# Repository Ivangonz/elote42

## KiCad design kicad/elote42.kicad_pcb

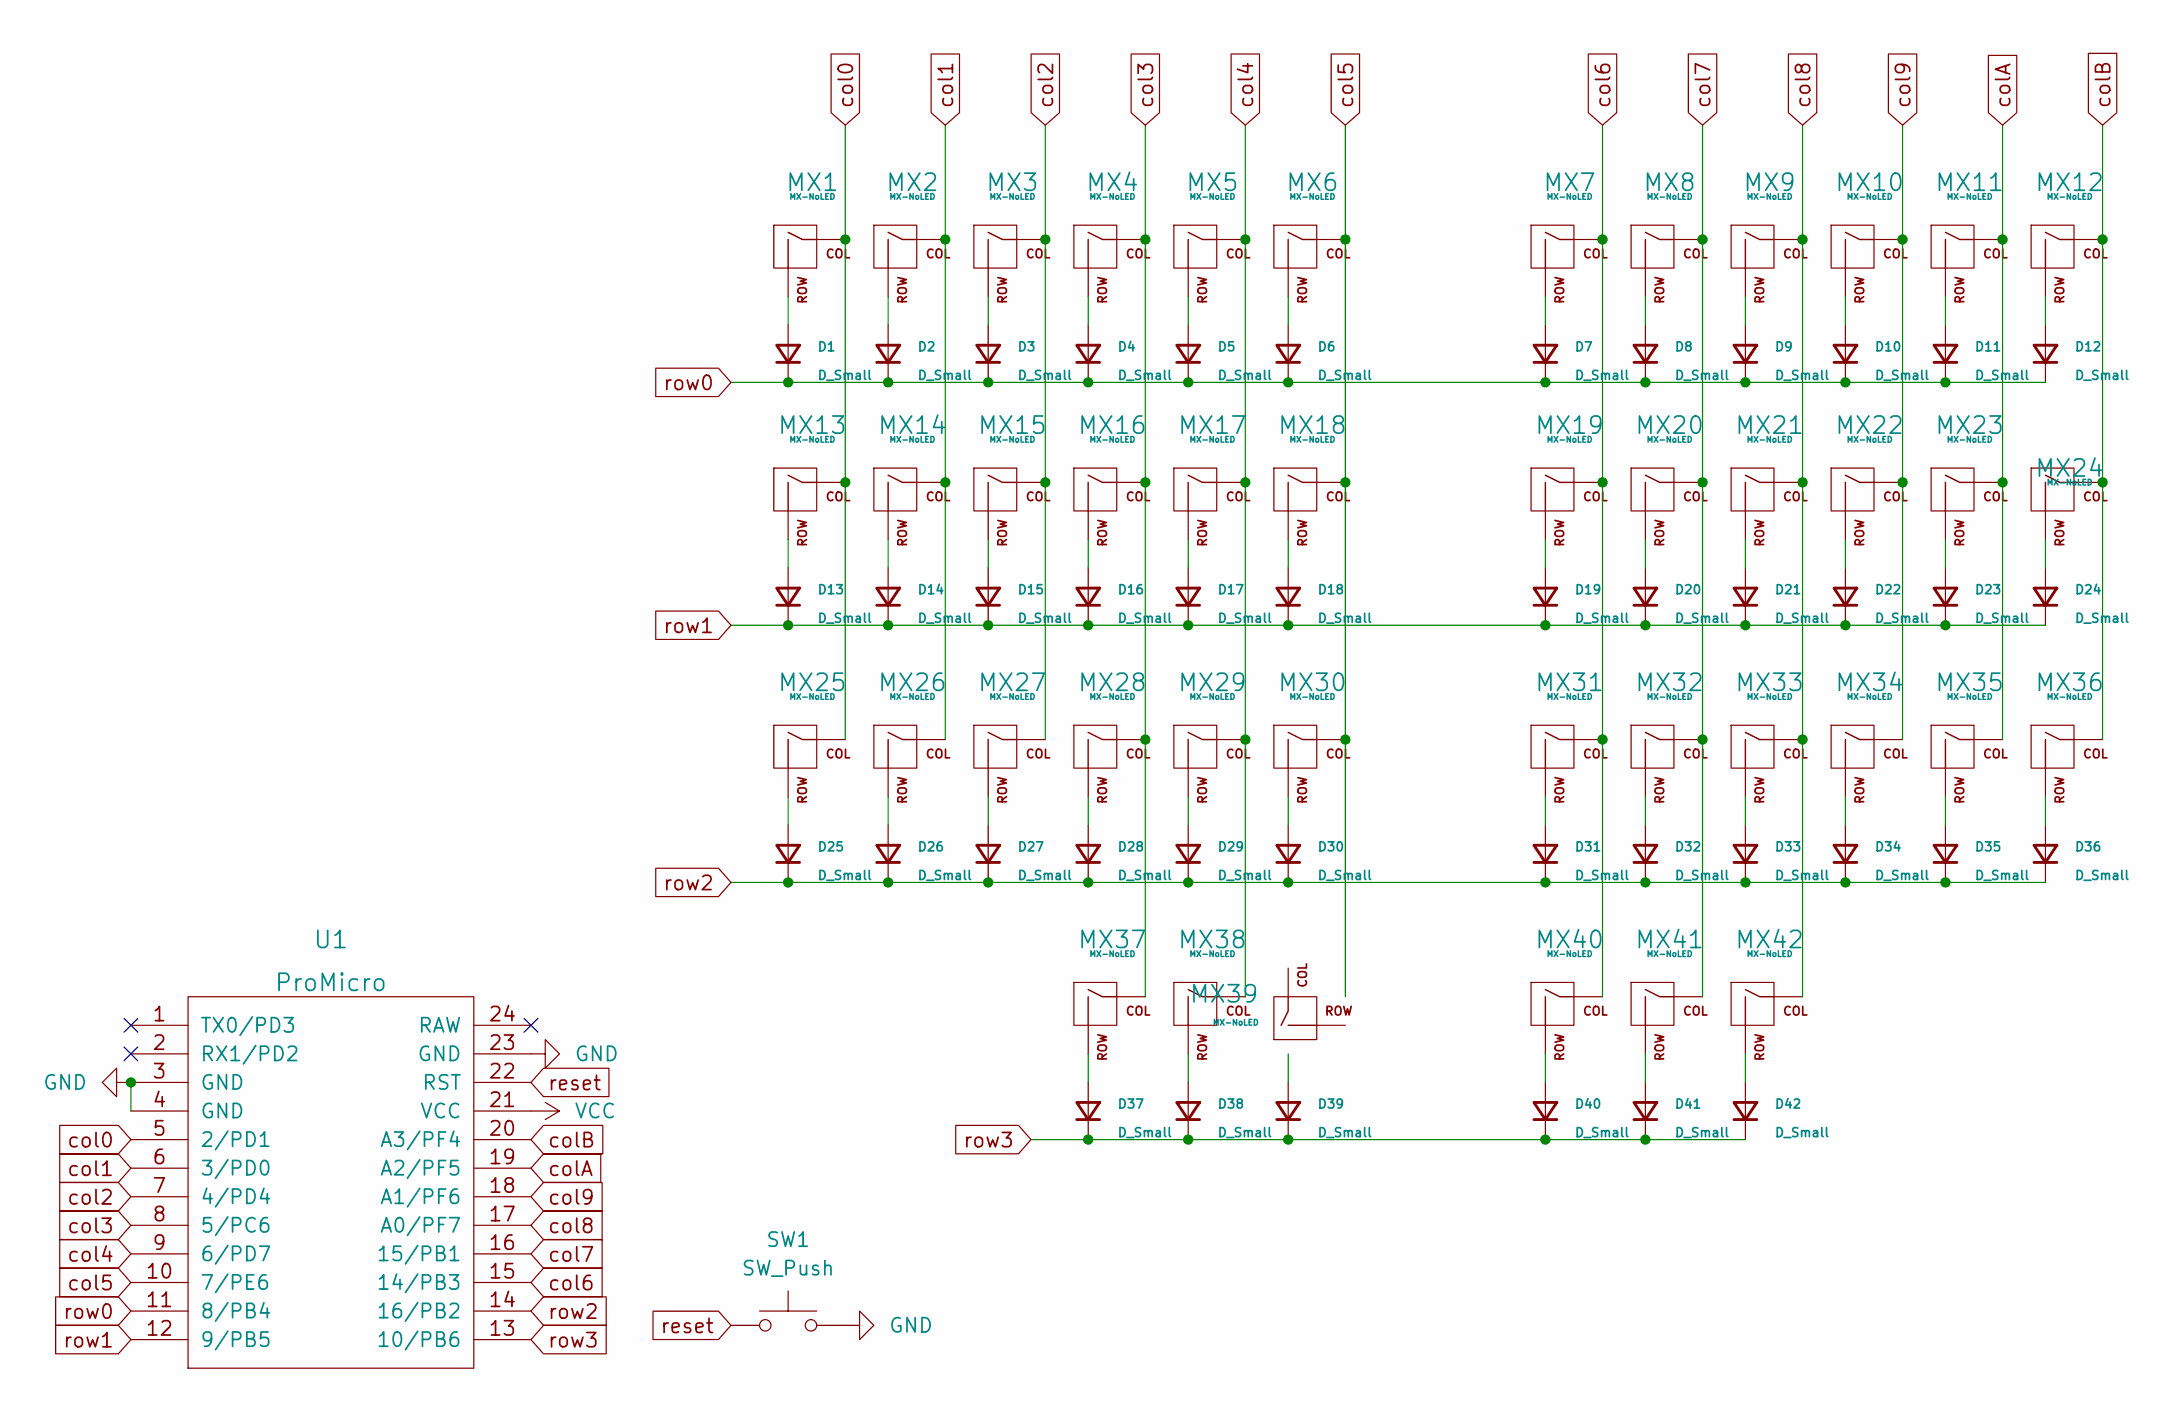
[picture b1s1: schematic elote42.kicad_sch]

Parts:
D1, D2, D3, D4, D5, D6, D7, D8, D9, D10, D11, D12, D13, D14, D15, D16, D17, D18, D19, D20, D21, D22, D23, D24, D25, D26, D27, D28, D29, D30, D31, D32, D33, D34, D35, D36, D37, D38, D39, D40, D41, D42: D_Small; Diode-dual
MX1, MX2, MX3, MX4, MX5, MX6, MX7, MX8, MX9, MX10, MX11, MX12, MX13, MX14, MX15, MX16, MX17, MX18, MX19, MX20, MX21, MX22, MX23, MX24, MX25, MX26, MX27, MX28, MX29, MX30, MX31, MX32, MX33, MX34, MX35, MX36, MX37, MX38, MX39, MX40, MX41, MX42: MX-NoLED; MX-1U-NoLED
SW1: SW_Push; SKQG-1155865
U1: ProMicro; ArduinoProMicro

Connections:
GND: SW1.2, U1.3 (GND), U1.4 (GND), U1.23 (GND)
unnamed: D1.2 (A), MX1.2 (ROW)
unnamed: D2.2 (A), MX2.2 (ROW)
unnamed: D3.2 (A), MX3.2 (ROW)
unnamed: D4.2 (A), MX4.2 (ROW)
unnamed: D5.2 (A), MX5.2 (ROW)
unnamed: D6.2 (A), MX6.2 (ROW)
unnamed: D7.2 (A), MX7.2 (ROW)
unnamed: D8.2 (A), MX8.2 (ROW)
unnamed: D9.2 (A), MX9.2 (ROW)
unnamed: D10.2 (A), MX10.2 (ROW)
unnamed: D11.2 (A), MX11.2 (ROW)
unnamed: D13.2 (A), MX13.2 (ROW)
unnamed: D14.2 (A), MX14.2 (ROW)
unnamed: D15.2 (A), MX15.2 (ROW)
unnamed: D16.2 (A), MX16.2 (ROW)
unnamed: D17.2 (A), MX17.2 (ROW)
unnamed: D18.2 (A), MX18.2 (ROW)
unnamed: D19.2 (A), MX19.2 (ROW)
unnamed: D20.2 (A), MX20.2 (ROW)
unnamed: D21.2 (A), MX21.2 (ROW)
unnamed: D22.2 (A), MX22.2 (ROW)
unnamed: D23.2 (A), MX23.2 (ROW)
unnamed: D24.2 (A), MX24.2 (ROW)
unnamed: D25.2 (A), MX25.2 (ROW)
unnamed: D26.2 (A), MX26.2 (ROW)
unnamed: D27.2 (A), MX27.2 (ROW)
unnamed: D28.2 (A), MX28.2 (ROW)
unnamed: D29.2 (A), MX29.2 (ROW)
unnamed: D30.2 (A), MX30.2 (ROW)
unnamed: D31.2 (A), MX31.2 (ROW)
unnamed: D32.2 (A), MX32.2 (ROW)
unnamed: D33.2 (A), MX33.2 (ROW)
unnamed: D34.2 (A), MX34.2 (ROW)
unnamed: D35.2 (A), MX35.2 (ROW)
unnamed: D36.2 (A), MX36.2 (ROW)
unnamed: D37.2 (A), MX37.2 (ROW)
unnamed: D38.2 (A), MX38.2 (ROW)
unnamed: D40.2 (A), MX40.2 (ROW)
unnamed: D41.2 (A), MX41.2 (ROW)
unnamed: D42.2 (A), MX42.2 (ROW)
unnamed: D12.2 (A), MX12.2 (ROW)
VCC: U1.21 (VCC)
col0: MX1.1 (COL), MX13.1 (COL), MX25.1 (COL), U1.5 (2/PD1)
col1: MX2.1 (COL), MX14.1 (COL), MX26.1 (COL), U1.6 (3/PD0)
col2: MX3.1 (COL), MX15.1 (COL), MX27.1 (COL), U1.7 (4/PD4)
col3: MX4.1 (COL), MX16.1 (COL), MX28.1 (COL), MX37.1 (COL), U1.8 (5/PC6)
col4: MX5.1 (COL), MX17.1 (COL), MX29.1 (COL), MX38.1 (COL), U1.9 (6/PD7)
col5: MX6.1 (COL), MX18.1 (COL), MX30.1 (COL), U1.10 (7/PE6)
col6: MX7.1 (COL), MX19.1 (COL), MX31.1 (COL), MX40.1 (COL), U1.15 (14/PB3)
col7: MX8.1 (COL), MX20.1 (COL), MX32.1 (COL), MX41.1 (COL), U1.16 (15/PB1)
col8: MX9.1 (COL), MX21.1 (COL), MX33.1 (COL), MX42.1 (COL), U1.17 (A0/PF7)
col9: MX10.1 (COL), MX22.1 (COL), MX34.1 (COL), U1.18 (A1/PF6)
colA: MX11.1 (COL), MX23.1 (COL), MX35.1 (COL), U1.19 (A2/PF5)
colB: MX12.1 (COL), MX24.1 (COL), MX36.1 (COL), U1.20 (A3/PF4)
reset: SW1.1, U1.22 (RST)
row0: D1.1 (K), D2.1 (K), D3.1 (K), D4.1 (K), D5.1 (K), D6.1 (K), D7.1 (K), D8.1 (K), D9.1 (K), D10.1 (K), D11.1 (K), D12.1 (K), U1.11 (8/PB4)
row1: D13.1 (K), D14.1 (K), D15.1 (K), D16.1 (K), D17.1 (K), D18.1 (K), D19.1 (K), D20.1 (K), D21.1 (K), D22.1 (K), D23.1 (K), D24.1 (K), U1.12 (9/PB5)
row2: D25.1 (K), D26.1 (K), D27.1 (K), D28.1 (K), D29.1 (K), D30.1 (K), D31.1 (K), D32.1 (K), D33.1 (K), D34.1 (K), D35.1 (K), D36.1 (K), U1.14 (16/PB2)
row3: D37.1 (K), D38.1 (K), D39.1 (K), D40.1 (K), D41.1 (K), D42.1 (K), U1.13 (10/PB6)

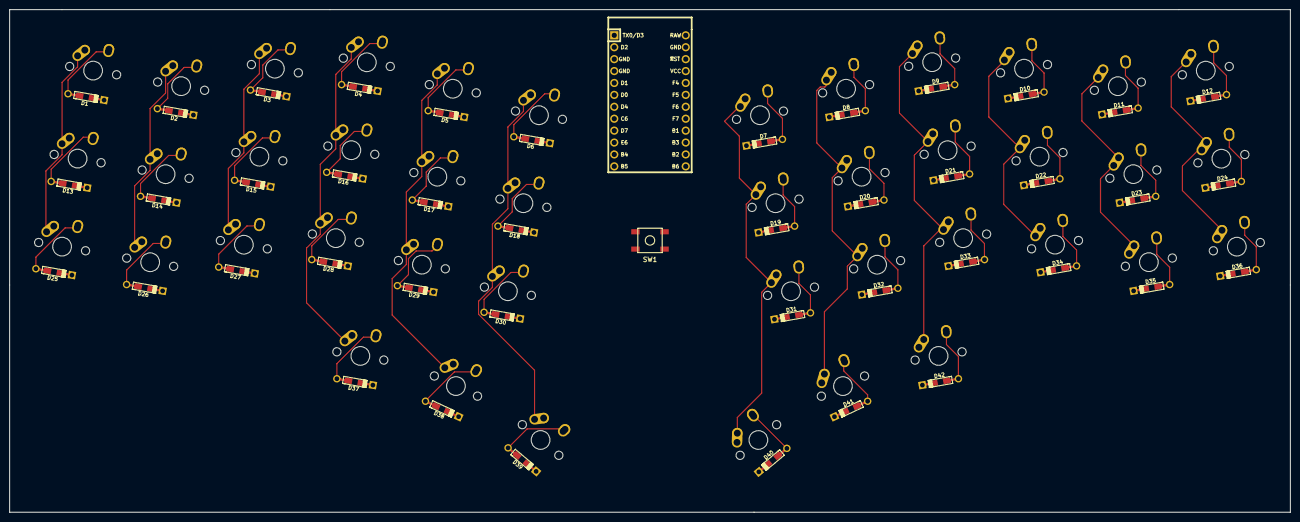
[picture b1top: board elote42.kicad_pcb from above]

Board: 2 copper layers, 273.1 x 107.2 mm, 86 parts (0 on the bottom side), 59 nets.

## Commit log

2022-06-03 Added keyboard libraries
2022-06-03 Added switches library
2022-06-03 Updated symbol libraries
2022-06-03 Resetting libraries
2022-06-03 finished schematics
2022-06-04 cleaned up directories
2022-06-04 Placed components on PCB
2022-06-04 Moved pads closer to MCU
2022-06-04 tilted pads 10 degrees and tightened distance to mcu
2022-06-04 Routed columns on left and right pads
2022-06-04 Routed diodes to corresponding switches
2022-06-04 flipped diodes on right side for easier routing
2022-06-04 row orientation swapped
